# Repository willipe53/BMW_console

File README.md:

# BMW_console
1974 BMW 2002 instrument cluster mod

This is a hack that uses a 3D part to hold two servos and an ESP32 in place inside a ripped up instrument cluster for the 1974 BMW 2002. As you will see from  [BMW_console.ino](BMW_console.ino), the microcontroller reads resistance values from pins `A3` and `A4` and moves the servos connected to pins `A0` and `A1` accordingly.

Granularity, min and max values for senders and servos can all be set from the serial monitor.  [Servo Holder.3mf](Servo Holder.3mf) is included for printing the servo holder.  It was created using Fusion 360.

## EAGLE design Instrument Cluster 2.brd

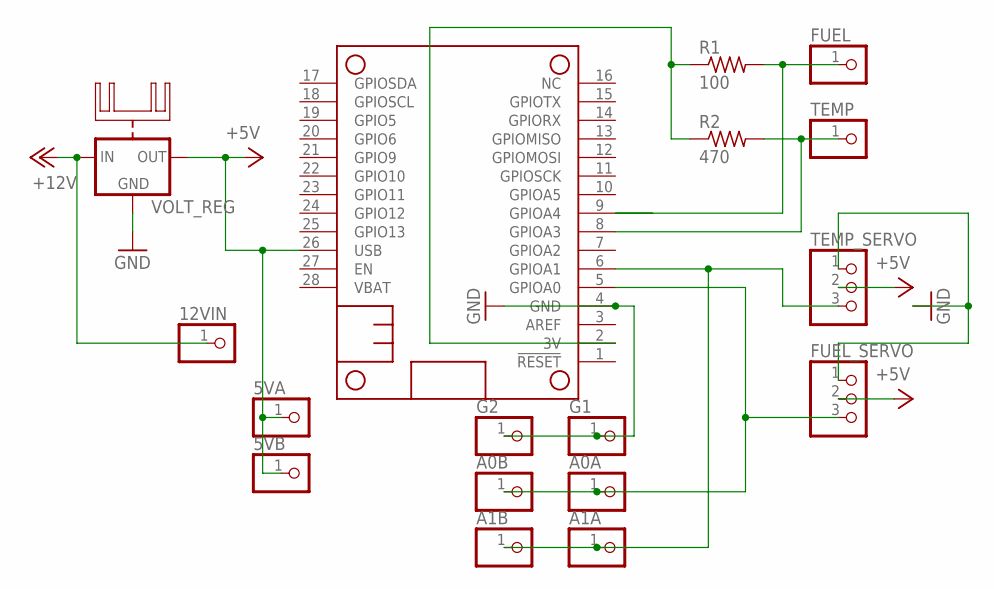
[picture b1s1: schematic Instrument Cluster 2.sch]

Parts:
5VA, 5VB, 12VIN: PINHD-1X1; 1X01
A0A, A0B, A1A, A1B: PINHD-1X1; 1X01
FUEL: PINHD-1X1; 1X01
FUEL_SERVO: PINHD-1X3; 1X03
G1, G2: PINHD-1X1; 1X01
MS2: FEATHERWING_NODIM; FEATHERWING_DIM
R1: 100; 0309/12
R2: 470; 0309/12
TEMP: PINHD-1X1; 1X01
TEMP_SERVO: PINHD-1X3; 1X03
VOLT_REG: 78XXH

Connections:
3V: MS2.2 (3V), R1.1, R2.1
+5V: 5VA.1, 5VB.1, FUEL_SERVO.2, MS2.26 (USB), TEMP_SERVO.2, VOLT_REG.OUT
+12V: 12VIN.1, VOLT_REG.IN
A0: A0A.1, A0B.1, FUEL_SERVO.3, MS2.5 (GPIOA0)
A1: A1A.1, A1B.1, MS2.6 (GPIOA1), TEMP_SERVO.3
A3: MS2.8 (GPIOA3), R2.2, TEMP.1
A4: FUEL.1, MS2.9 (GPIOA4), R1.2
GND: FUEL_SERVO.1, G1.1, G2.1, MS2.4 (GND), TEMP_SERVO.1, VOLT_REG.GND

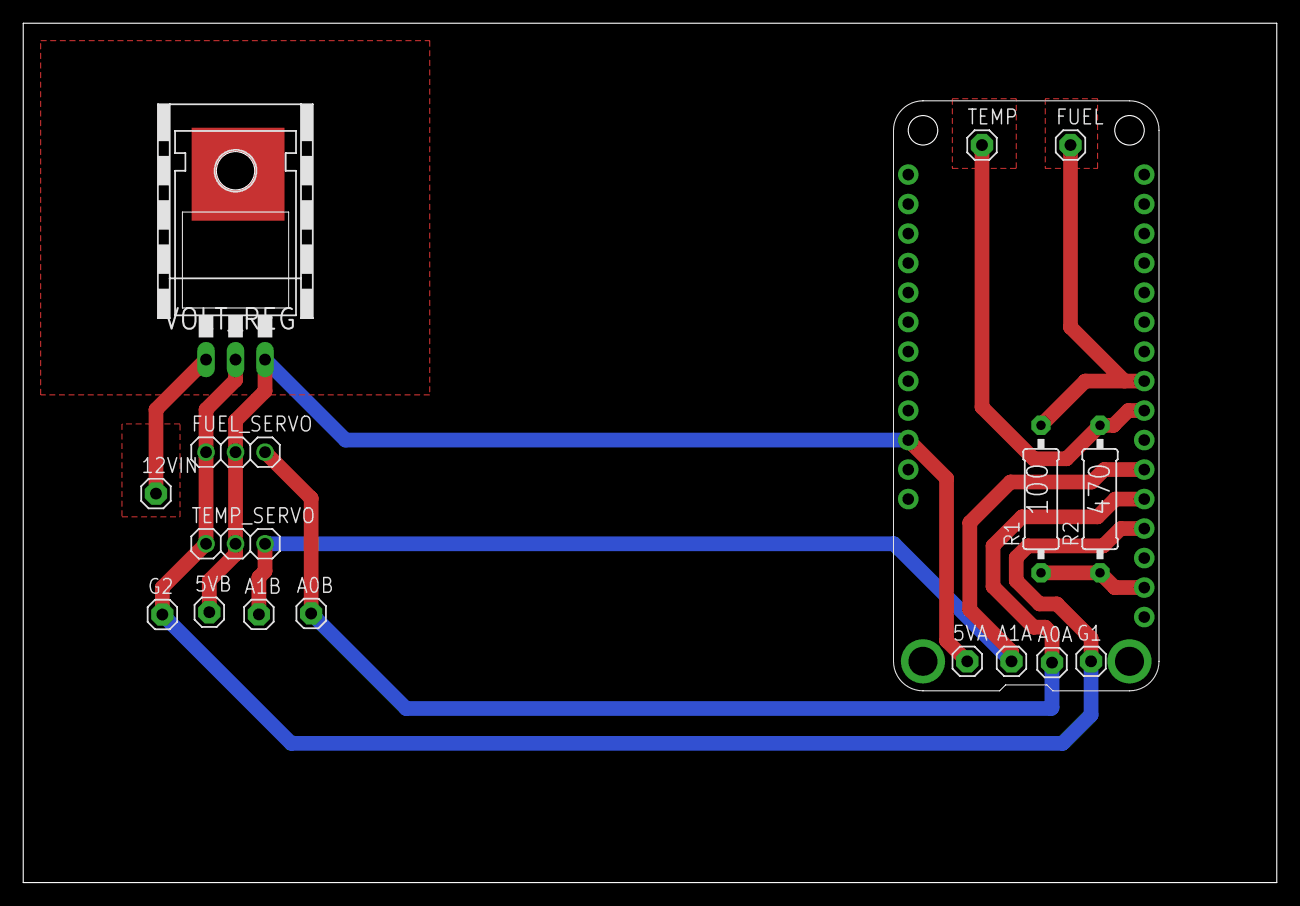
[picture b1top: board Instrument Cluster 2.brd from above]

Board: 2 copper layers, 107.9 x 74.0 mm, 17 parts (0 on the bottom side), 8 nets.

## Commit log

2022-10-09 Updated documentation
